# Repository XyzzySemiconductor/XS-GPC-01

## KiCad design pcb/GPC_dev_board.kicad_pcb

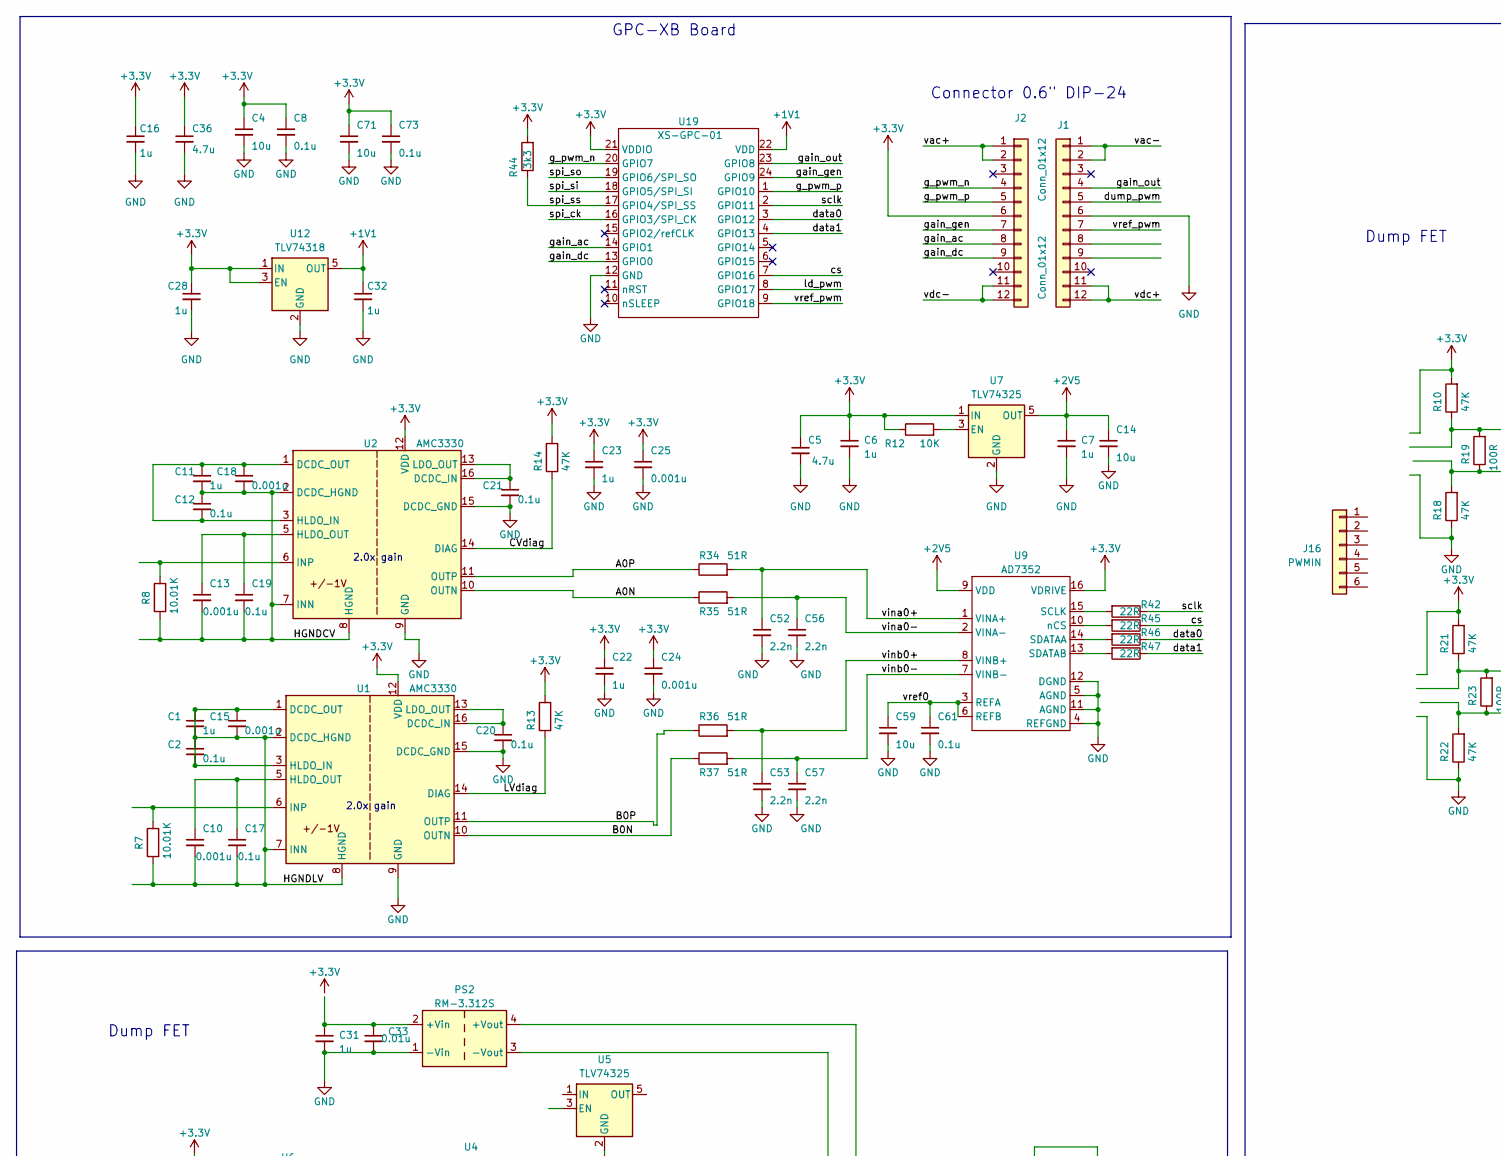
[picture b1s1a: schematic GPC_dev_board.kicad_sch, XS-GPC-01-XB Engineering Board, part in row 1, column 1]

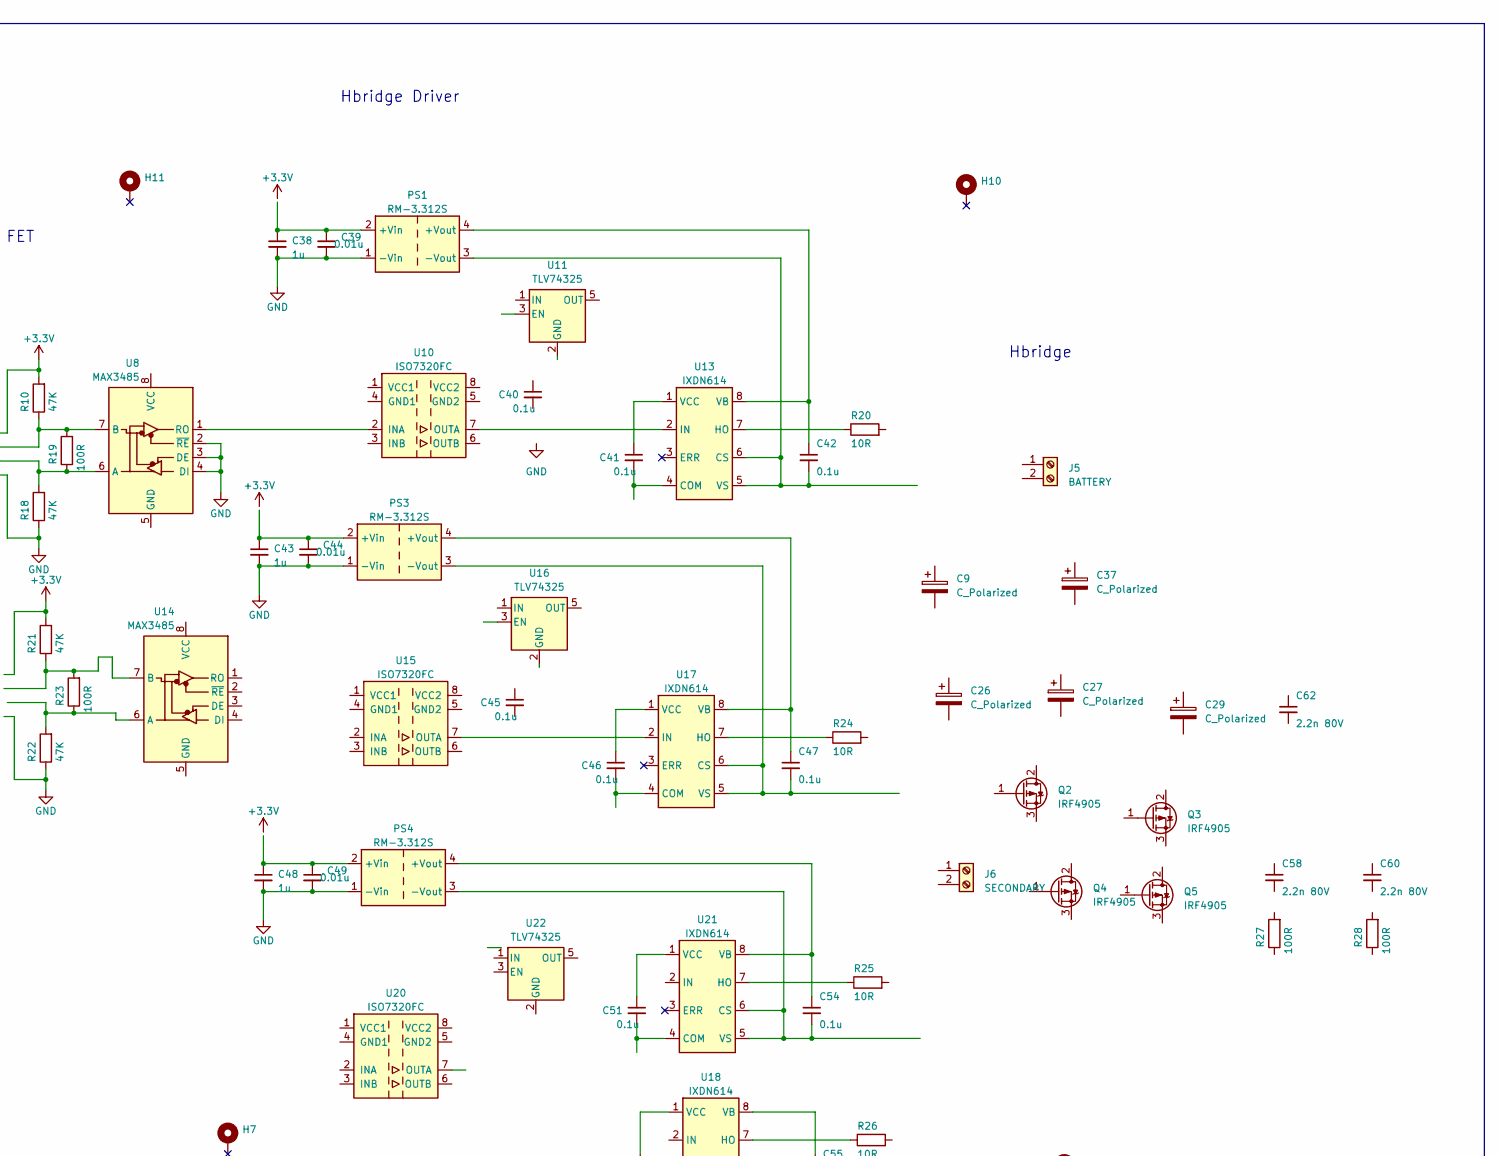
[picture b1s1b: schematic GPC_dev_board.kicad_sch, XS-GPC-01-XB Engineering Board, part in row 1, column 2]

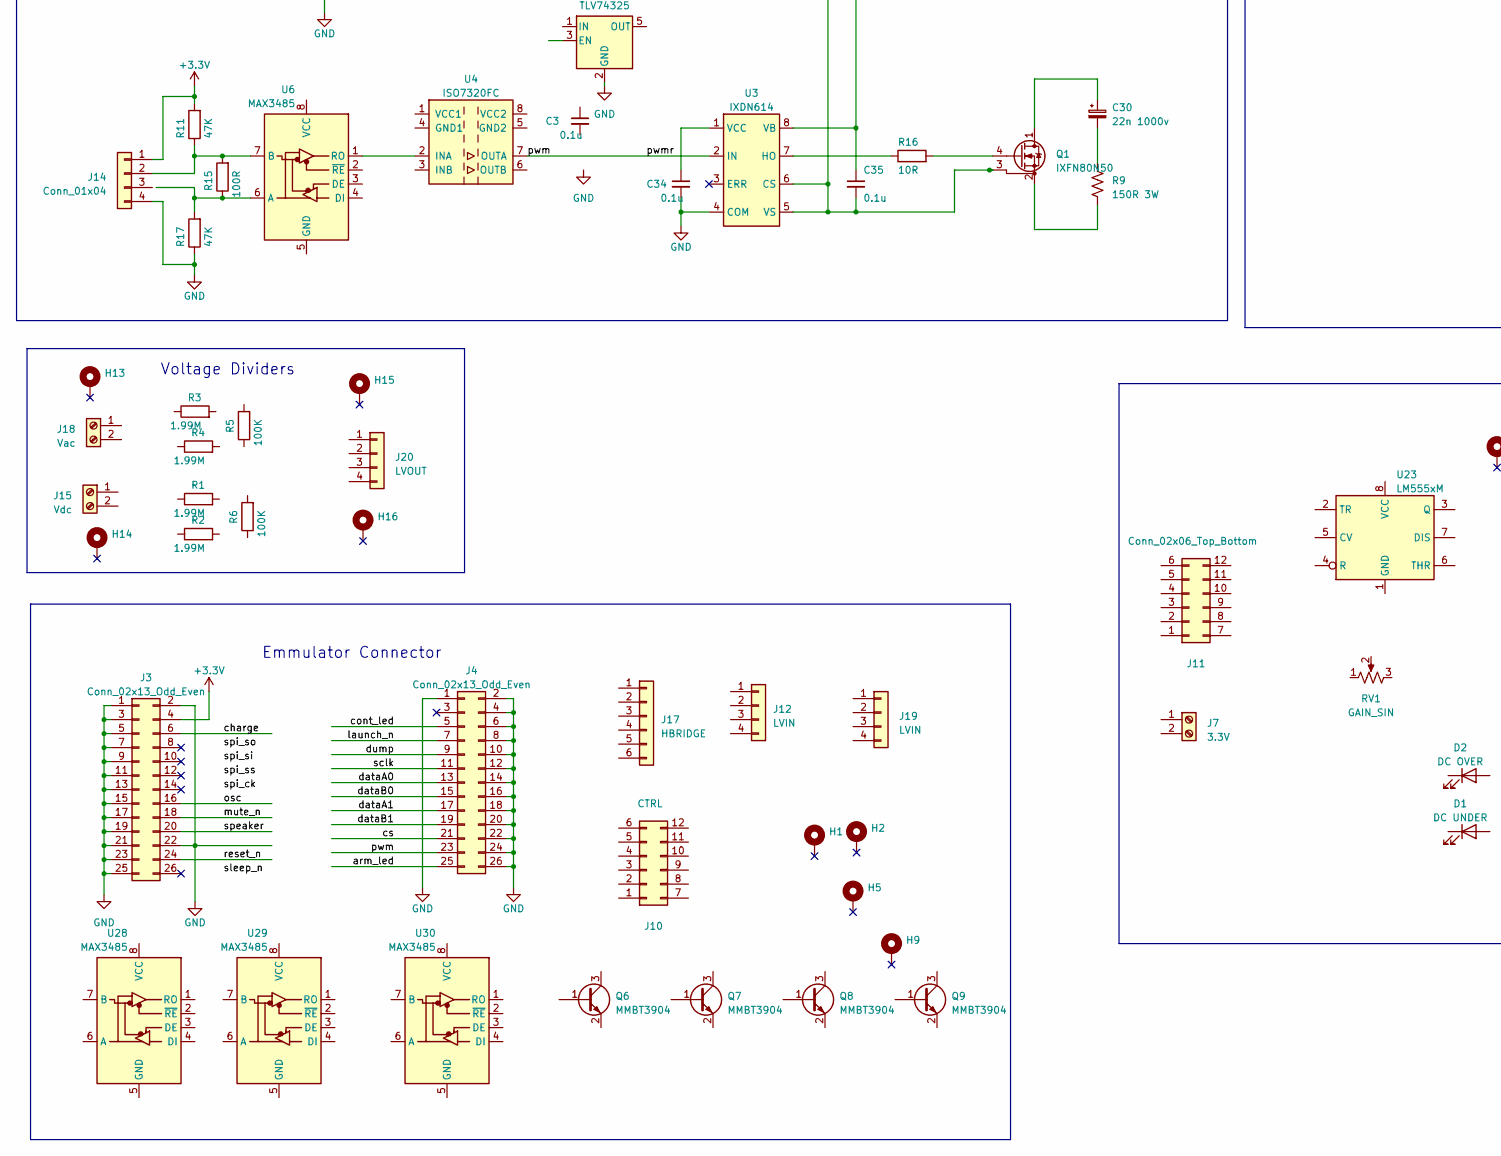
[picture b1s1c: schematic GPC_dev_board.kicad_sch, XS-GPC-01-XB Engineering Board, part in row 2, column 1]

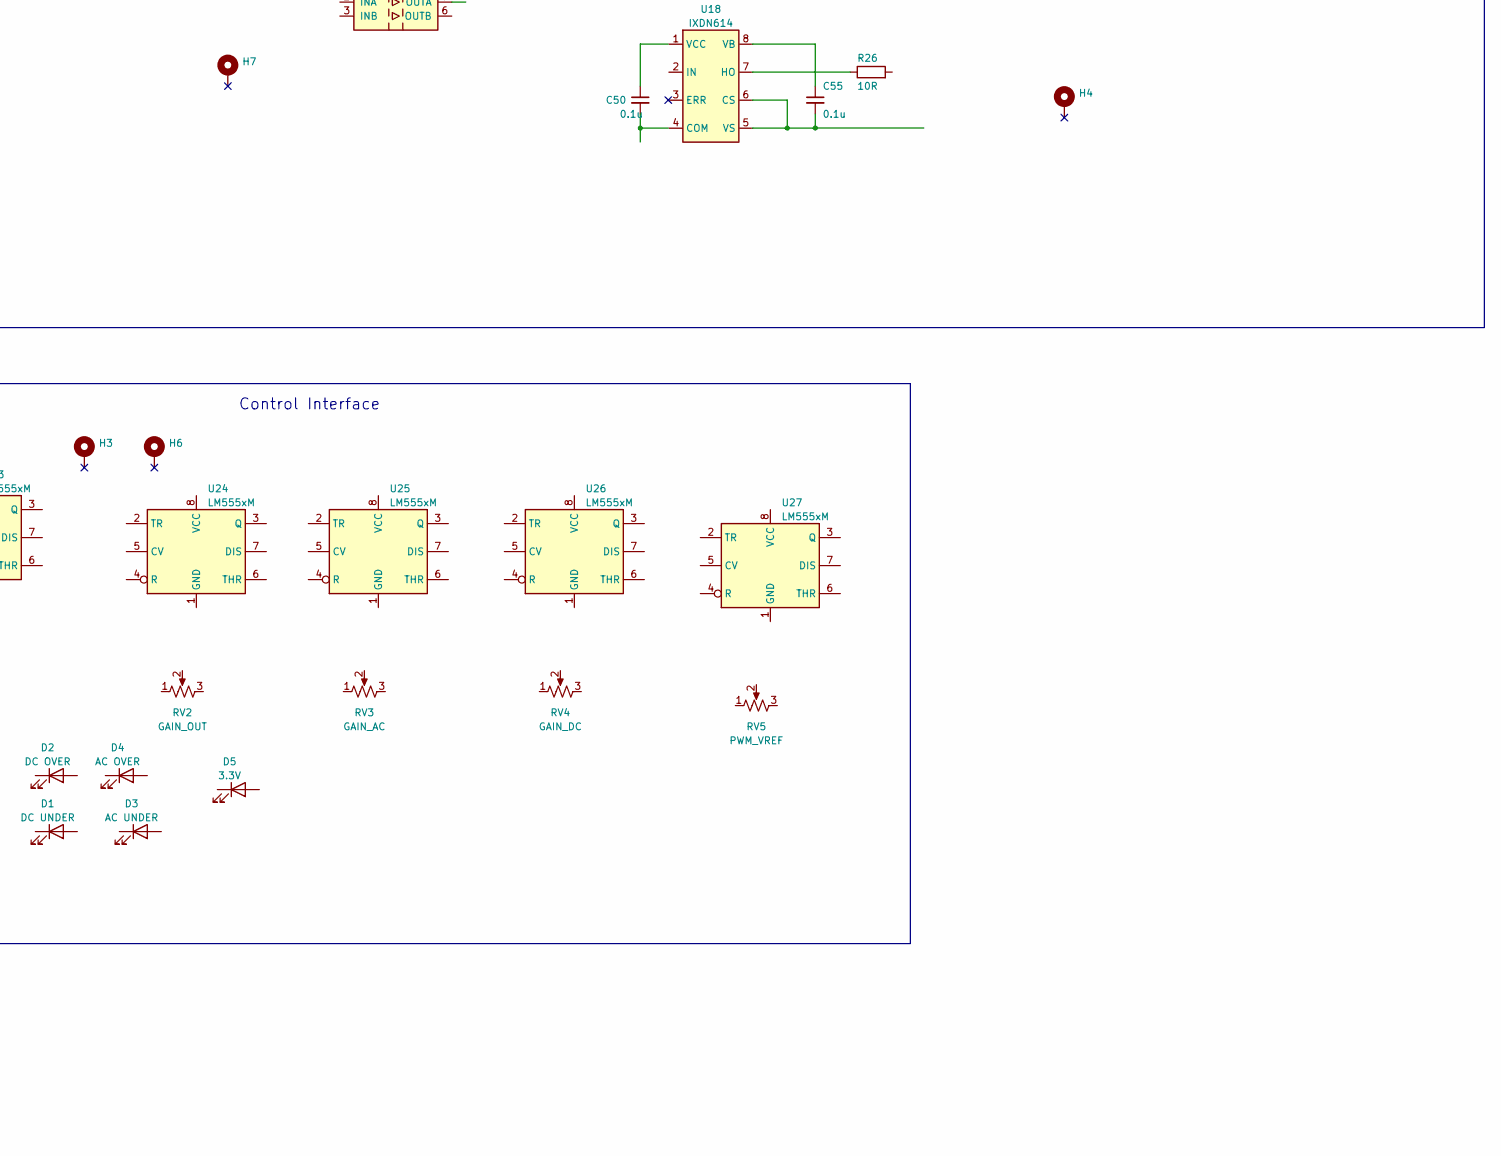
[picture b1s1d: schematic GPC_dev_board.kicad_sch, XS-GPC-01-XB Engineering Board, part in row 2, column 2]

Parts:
C1, C6, C7, C11, C16, C22, C23, C28, C31, C32, C38, C43, C48: 1u; C_0603_1608Metric
C2, C3, C8, C12, C17, C19, C20, C21, C34, C35, C40, C41, C42, C45, C46, C47, C50, C51, C54, C55, C61, C73: 0.1u; C_0603_1608Metric
C4, C14, C59, C71: 10u; C_1206_3216Metric
C5, C36: 4.7u; C_1206_3216Metric
C9, C26, C27, C29, C37: C_Polarized; CP_Radial_D10.0mm_P5.00mm
C10, C13, C15, C18, C24, C25: 0.001u; C_0603_1608Metric
C30: 22n 1000v; C_Rect_L13.0mm_W6.0mm_P10.00mm_FKS3_FKP3_MKS4
C33, C39, C44, C49: 0.01u; C_0603_1608Metric
C52, C53, C56, C57: 2.2n; C_0603_1608Metric
C58, C60, C62: 2.2n 80V; C_0603_1608Metric
D1: DC UNDER; LED_0603_1608Metric
D2: DC OVER; LED_0603_1608Metric
D3: AC UNDER; LED_0603_1608Metric
D4: AC OVER; LED_0603_1608Metric
D5: 3.3V; LED_0603_1608Metric
H1, H2, H3, H4, H5, H6, H7, H9, H10, H11, H13, H14, H15, H16: MountingHole_3mm_Pad
J1, J2: Conn_01x12; PinHeader_1x12_P2.54mm_Vertical
J3, J4: Conn_02x13_Odd_Even; PinSocket_2x13_P2.54mm_Vertical
J5: BATTERY; TerminalBlock_Phoenix_MKDS-1,5-2-5.08_1x02_P5.08mm_Horizont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
J6: SECONDARY; TerminalBlock_Phoenix_MKDS-1,5-2-5.08_1x02_P5.08mm_Horizont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
J7: 3.3V; TerminalBlock_Phoenix_MKDS-1,5-2-5.08_1x02_P5.08mm_Horizont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
J10: CTRL; PinHeader_2x06_P2.54mm_Vertical
J11: Conn_02x06_Top_Bottom; PinHeader_2x06_P2.54mm_Horizontal
J12, J19: LVIN; PinHeader_1x04_P2.54mm_Vertical
J14: Conn_01x04; PinHeader_1x04_P2.54mm_Horizontal
J15: Vdc; TerminalBlock_Phoenix_MKDS-1,5-2-5.08_1x02_P5.08mm_Horizont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
J16: PWMIN; PinHeader_1x06_P2.54mm_Horizontal
J17: HBRIDGE; PinHeader_1x06_P2.54mm_Vertical
J18: Vac; TerminalBlock_Phoenix_MKDS-1,5-2-5.08_1x02_P5.08mm_Horizont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
J20: LVOUT; PinHeader_1x04_P2.54mm_Horizontal
PS1, PS2, PS3, PS4: RM-3.312S; Converter_DCDC_Murata_MEE1SxxxxSC_THT
Q1: IXFN80N50; SOT-227
Q2, Q3, Q4, Q5: IRF4905; TO-220-3_Horizontal_TabDown
Q6, Q7, Q8, Q9: MMBT3904; SOT-23
R1, R2, R3, R4: 1.99M; R_2512_6332Metric; JLC C778416
R5, R6: 100K; R_2512_6332Metric; JLC C778416
R7, R8: 10.01K; R_0603_1608Metric; JLC C778416
R9: 150R 3W; R_2512_6332Metric
R10, R11, R13, R14, R17, R18, R21, R22: 47K; R_0603_1608Metric; JLC C778416
R12: 10K; R_0603_1608Metric; JLC C778416
R15, R19, R23, R27, R28: 100R; R_0603_1608Metric; JLC C778416
R16, R20, R24, R25, R26: 10R; R_0603_1608Metric; JLC C778416
R34, R35, R36, R37: 51R; R_0603_1608Metric; JLC C778416
R42, R45, R46, R47: 22R; R_0603_1608Metric; JLC C319967
R44: 3k3; R_0603_1608Metric; JLC C319967
RV1: GAIN_SIN; Potentiometer_Bourns_3299X_Horizontal
RV2: GAIN_OUT; Potentiometer_Bourns_3299X_Horizontal
RV3: GAIN_AC; Potentiometer_Bourns_3299X_Horizontal
RV4: GAIN_DC; Potentiometer_Bourns_3299X_Horizontal
RV5: PWM_VREF; Potentiometer_Bourns_3299X_Horizontal
U1, U2: AMC3330; SOIC-16W_7.5x10.3mm_P1.27mm
U3, U13, U17, U18, U21: IXDN614; SOIC-8_3.9x4.9mm_P1.27mm
U4, U10, U15, U20: ISO7320FC; SOIC-8_3.9x4.9mm_P1.27mm
U5, U7, U11, U16, U22: TLV74325; SOT-23-5
U6, U8, U14, U28, U29, U30: MAX3485; SOIC-8_3.9x4.9mm_P1.27mm
U9: AD7352; TSSOP-16_4.4x5mm_P0.65mm
U12: TLV74318; SOT-23-5
U19: XS-GPC-01; QFN-24-3x3mm
U23, U24, U25, U26, U27: LM555xM; SOIC-8_3.9x4.9mm_P1.27mm

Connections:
+1V1: C32.1, U12.5 (OUT), U19.22 (VDD)
+2V5: C7.1, C14.1, U7.5 (OUT), U9.9 (VDD)
+3.3V: C4.1, C5.1, C6.1, C8.1, C16.1, C22.1, C23.1, C24.1, C25.1, C28.1, C36.1, C71.1, C73.1, J2.6, J3.4, J14.1, R10.2, R11.2, R12.1, R13.2, R14.2, R21.2, R44.2, U1.12 (VDD), U2.12 (VDD), U7.1 (IN), U9.16 (VDRIVE), U12.1 (IN), U12.3 (EN), U19.21 (VDDIO)
/A0N: R35.1, U2.10 (OUTN)
/A0P: R34.1, U2.11 (OUTP)
/B0N: R37.1, U1.10 (OUTN)
/B0P: R36.1, U1.11 (OUTP)
/CVdiag: R14.1, U2.14 (DIAG)
/HGNDCV: C11.2, C12.1, C13.2, C18.2, C19.2, R8.1, U2.2 (DCDC_HGND), U2.7 (INN), U2.8 (HGND)
/HGNDLV: C1.1, C1.2, C2.1, C2.2, C10.2, C15.1, C15.2, C17.2, R7.1, U1.1 (DCDC_OUT), U1.2 (DCDC_HGND), U1.3 (HLDO_IN), U1.7 (INN), U1.8 (HGND)
/LVdiag: R13.1, U1.14 (DIAG)
/arm_led: J4.25
/charge: J3.6
/cont_led: J4.5
/cs: J4.21, R45.1, U19.7 (GPIO16)
/data0: R46.1, U19.3 (GPIO12)
/data1: R47.1, U19.4 (GPIO13)
/dataA0: J4.13
/dataA1: J4.17
/dataB0: J4.15
/dataB1: J4.19
/dump: J4.9
/dump_pwm: J1.5
/g_pwm_n: J2.4, U19.20 (GPIO7)
/g_pwm_p: J2.5, U19.1 (GPIO10)
/gain_ac: J2.8, U19.14 (GPIO1)
/gain_dc: J2.9, U19.13 (GPIO0)
/gain_gen: J2.7, U19.24 (GPIO9)
/gain_out: J1.4, U19.23 (GPIO8)
/launch_n: J4.7
/ld_pwm: U19.8 (GPIO17)
/mute_n: J3.18
/osc: J3.16
/pwm: J4.23, U4.7 (OUTA)
/reset_n: J3.24
/sclk: J4.11, R42.1, U19.2 (GPIO11)
/speaker: J3.20
/spi_ck: U19.16 (GPIO3/SPI_CK)
/spi_si: U19.18 (GPIO5/SPI_SI)
/spi_so: U19.19 (GPIO6/SPI_SO)
/spi_ss: R44.1, U19.17 (GPIO4/SPI_SS)
/vac+: J2.1, J2.2
/vac-: J1.1, J1.2
/vdc+: J1.11, J1.12
/vdc-: J2.11, J2.12
/vina0+: C52.1, R34.2, U9.1 (VINA+)
/vina0-: C56.1, R35.2, U9.2 (VINA-)
/vinb0+: C53.1, R36.2, U9.8 (VINB+)
/vinb0-: C57.1, R37.2, U9.7 (VINB-)
/vref0: C59.1, C61.1, U9.3 (REFA), U9.6 (REFB)
/vref_pwm: J1.7, U19.9 (GPIO18)
GND: C4.2, C5.2, C6.2, C7.2, C8.2, C14.2, C16.2, C20.2, C21.2, C22.2, C23.2, C24.2, C25.2, C28.2, C31.2, C32.2, C33.2, C34.2, C36.2, C38.2, C39.2, C43.2, C44.2, C48.2, C49.2, C52.2, C53.2, C56.2, C57.2, C59.2, C61.2, C71.2, C73.2, J1.6, J3.1, J3.2, J3.3, J3.5, J3.7, J3.9, J3.11, J3.13, J3.15, J3.17, J3.19, J3.21, J3.22, J3.23, J3.25, J4.1, J4.2, J4.4, J4.6, J4.8, J4.10, J4.12, J4.14, J4.16, J4.18, J4.20, J4.22, J4.24, J4.26, J14.4, PS1.1 (-Vin), PS2.1 (-Vin), PS3.1 (-Vin), PS4.1 (-Vin), R17.1, R18.1, R22.1, U1.9 (GND), U1.15 (DCDC_GND), U2.9 (GND), U2.15 (DCDC_GND), U5.2 (GND), U7.2 (GND), U8.2 (~RE), U8.3 (DE), U8.4 (DI), U9.4 (REFGND), U9.5 (AGND), U9.11 (AGND), U9.12 (DGND), U12.2 (GND), U19.12 (GND)
unnamed: C30.2, R9.1
unnamed: J14.2, R11.1, R15.2, U6.7 (B)
unnamed: C38.1, C39.1, PS1.2 (+Vin)
unnamed: C42.1, PS1.4 (+Vout)
unnamed: C42.2, PS1.3 (-Vout)
unnamed: C31.1, C33.1, PS2.2 (+Vin)
unnamed: C35.1, PS2.4 (+Vout)
unnamed: C35.2, PS2.3 (-Vout), Q1.3 (DS)
unnamed: C43.1, C44.1, PS3.2 (+Vin)
unnamed: C47.1, PS3.4 (+Vout)
unnamed: C47.2, PS3.3 (-Vout)
unnamed: C48.1, C49.1, PS4.2 (+Vin)
unnamed: C54.1, PS4.4 (+Vout)
unnamed: C54.2, PS4.3 (-Vout)
unnamed: C30.1, Q1.1 (D)
unnamed: Q1.4 (G), R16.2
unnamed: Q1.2 (S), R9.2
unnamed: C20.1, U1.13 (LDO_OUT), U1.16 (DCDC_IN)
unnamed: C10.1, C17.1, U1.5 (HLDO_OUT)
unnamed: R7.2, U1.6 (INP)
unnamed: C21.1, U2.13 (LDO_OUT), U2.16 (DCDC_IN)
unnamed: C11.1, C12.2, C18.1, U2.1 (DCDC_OUT), U2.3 (HLDO_IN)
unnamed: C13.1, C19.1, U2.5 (HLDO_OUT)
unnamed: R8.2, U2.6 (INP)
unnamed: U4.2 (INA), U6.1 (RO)
unnamed: R15.1, R17.2, U6.6 (A)
unnamed: R12.2, U7.3 (EN)
unnamed: R18.2, R19.1, U8.6 (A)
unnamed: R10.1, R19.2, U8.7 (B)
unnamed: R42.2, U9.15 (SCLK)
unnamed: R46.2, U9.14 (SDATAA)
unnamed: R47.2, U9.13 (SDATAB)
unnamed: R45.2, U9.10 (nCS)
unnamed: U8.1 (RO), U10.2 (INA)
unnamed: R22.2, R23.1, U14.6 (A)
unnamed: R21.1, R23.2, U14.7 (B)

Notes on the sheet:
Connector 0.6" DIP-24
GPC-XB Board
Dump FET
2.0x gain
Voltage Dividers
Hbridge Driver
Control Interface
Emmulator Connector
Hbridge

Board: 6 copper layers, 185 parts (16 on the bottom side), 70 nets, no tracks yet.

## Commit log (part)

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2026-05-25 doc basic idea
2026-05-25 Update info yal with the deets
2026-05-26 Add cordic sine/cos
2026-05-26 array assign not supported
2026-05-26 wire up, tie off all inputs and outputs
2026-05-28 ADC interface, error accumlation, duty cycle calc, and load PWM
2026-05-29 Added fast delta driven pwm with gate and thresh inpuss
2026-05-29 Fix setup, registered the threshold decoder
2026-05-30 reworked load pwm to use gated |sin| for accumulatio and feedback
2026-05-31 Enhance documentation for ASIC project
    Expanded documentation for the 60 Hz Grid-Forming ASIC, detailing core features, I/O summary, intended use case, and testing requirements.
2026-06-01 Add 2nd ADC input channel for DClink voltage
2026-06-01 info.yaml syntax fix
2026-06-02 Add /clk output, see if tt flow accepts?
2026-06-02 Added adc model for testbench (and bist?)
2026-06-02 Dual loops (AC, DC) dump load control rough in
2026-06-02 Integration fixes
2026-06-03 Timing patch
2026-06-03 explict barrel shift help timing?
2026-06-03 pipeline logic, deal with area growth later
2026-06-03 fixup reg
2026-06-03 Change tile configuration from '2x2' to '1x2'
2026-06-05 brutalist vref modulator trial
2026-06-05 Grid power chip (GPC) datasheet and experiment application PCB
2026-06-06 Rename PCB files
2026-06-07 trimmed bit widths, tightened AC/DC loops
2026-06-07 Tightened up RTL for synth tool 95% utlized. Bitstream generated.
2026-06-07 Will table sin fit in 1x1?
2026-06-07 Back to 1x2 and half lut size
2026-06-08 Trim down to 128x9bit
2026-06-08 Reduce to 64x9 sin
2026-06-08 32x9 sin for 1x1
2026-06-08 Tighten dc_delta, dc vref pwm logic
2026-06-08 retarget to 1x2 <sigh>
2026-06-08 use cordic
2026-06-08 Implement reset for sin and absin signals
    Add reset logic to initialize sin and absin
2026-06-08 dc active and asserts on pwm output
2026-06-09 Add AC 1/4 cycle control gate
2026-06-09 Add testbench PWM generators
2026-06-09 remove tab from info.yaml
2026-06-10 cleanup for verilator
2026-06-11 Basics of system model roughed in and starting to run
2026-06-11 fix acc clips and dc low hysteresis
2026-06-11 stability window
2026-06-12 Add end of run sanity check that Dclink voltages finiahes in the controll range
2026-06-14 AC prescale 4x
2026-06-14 Added max10 fpga test bench. Rough but compiles. Needs system model yet
2026-06-15 Add synthesizable dc link model.
2026-06-15 Change over to integer model to simulate, and test GL
2026-06-15 include model for GL Sims
2026-06-15 Include model for sims
2026-06-16 TB Starting sine polarity should match dut
2026-06-17 Fixup system model LUT
2026-06-17 fpga drive speaker with generator sine pwm.
2026-06-17 fixup dclink model table
2026-06-17 Added disclaimer and clean up
    Removed backslashes from variable names for clarity and consistency.
2026-06-18 Dclink in control, while doubling poiwer steps to 3200W.
2026-06-18 artefact for 5d9083e (and fixup tt image size)
2026-06-18 max gain dc 4, ac 8 --> 1, 1 by pwm, and ac -limit == ac -thresh
2026-06-18 moved to 6KWatt sims on FPGA and added ac gain sweep test. gains are good.
2026-06-19 Add ac/dc over/under flags in uo_out[7:4]
2026-06-28 In process, Dev board topology PCB sections and floorplanning evolution.
